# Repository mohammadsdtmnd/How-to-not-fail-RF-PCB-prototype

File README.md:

# How to not fail RF PCB prototype
I've made GPS amplifier for hobby time, it failed. I've learned what I should not have done again to prevent failure. My motivation for doing this was to see the GPS signal spectrum. :) Note I had tried my best to minimize cost. For example by eliminating stensil and soldermask. Though still PCB is metalized with bot layer gnd. I think I could also not making it metalized. Making it stiching with thin wire, instead. Since metalizing caused my manufacturer to prolong a long time.

**You can look at schematic and PCB and see these strength:**

+ Simple
+ High gain
+ Extremely compact design
+ 0.25mm PCB thickness chosen to decrease track and match them to RF amps
+ small footprint which also causes them to be more stable because of less leakage

This compact design chosen to minimize distortion in GPS RF signal.

**PCB Weakness:**
  
+ 0.5mm pitch footprint is small for handsoldering
+ Amplifier package does not have edge lead tail, to make you certain about solder connectivity

But other than foot print and devices package chosen, tools are extremely important:

**Tools weakness:**
  
+ Bulky 60W iron used and caused catastrophy there :(
+ Use of thick solder wire
+ Lower melting point solder plus hot air could help success of assmbling but was missed

**Tools strength:**
  
+ Precise tweezer
+ Good lenz for zooming

And the thing I had really missed was to be patience to waint until accessing at least SMD specialized iron.

**Here is manufactured PCB:**

**Prepaird workbench:**

**First try success:**

**but the secound not:**

I had placed tip of my bulky iron beneath the IC and the resin of PCB burnd!! Though I've been dissapointed. I told OK. I will make the secound PCB with success.
The secound PCB had inherent wrong. It missed one track in sensitive area, Under amplifier. :(

But I managed to handle it with 0.1mm Wire, Low melting solder and Hot air

**And the result was promising:**

Though I've assembled all amplifier with success. Then I tried to place other components with my bulky iron and wire solder. Then another tack removed and caused to one amplifier being detached.

Now next time I will be sure to use smd iron.
Then all components should have more than 1mm pitch for handsoldering. Otherwise I should have sharp tip iron with low melting point solder if possible. Plus patience.

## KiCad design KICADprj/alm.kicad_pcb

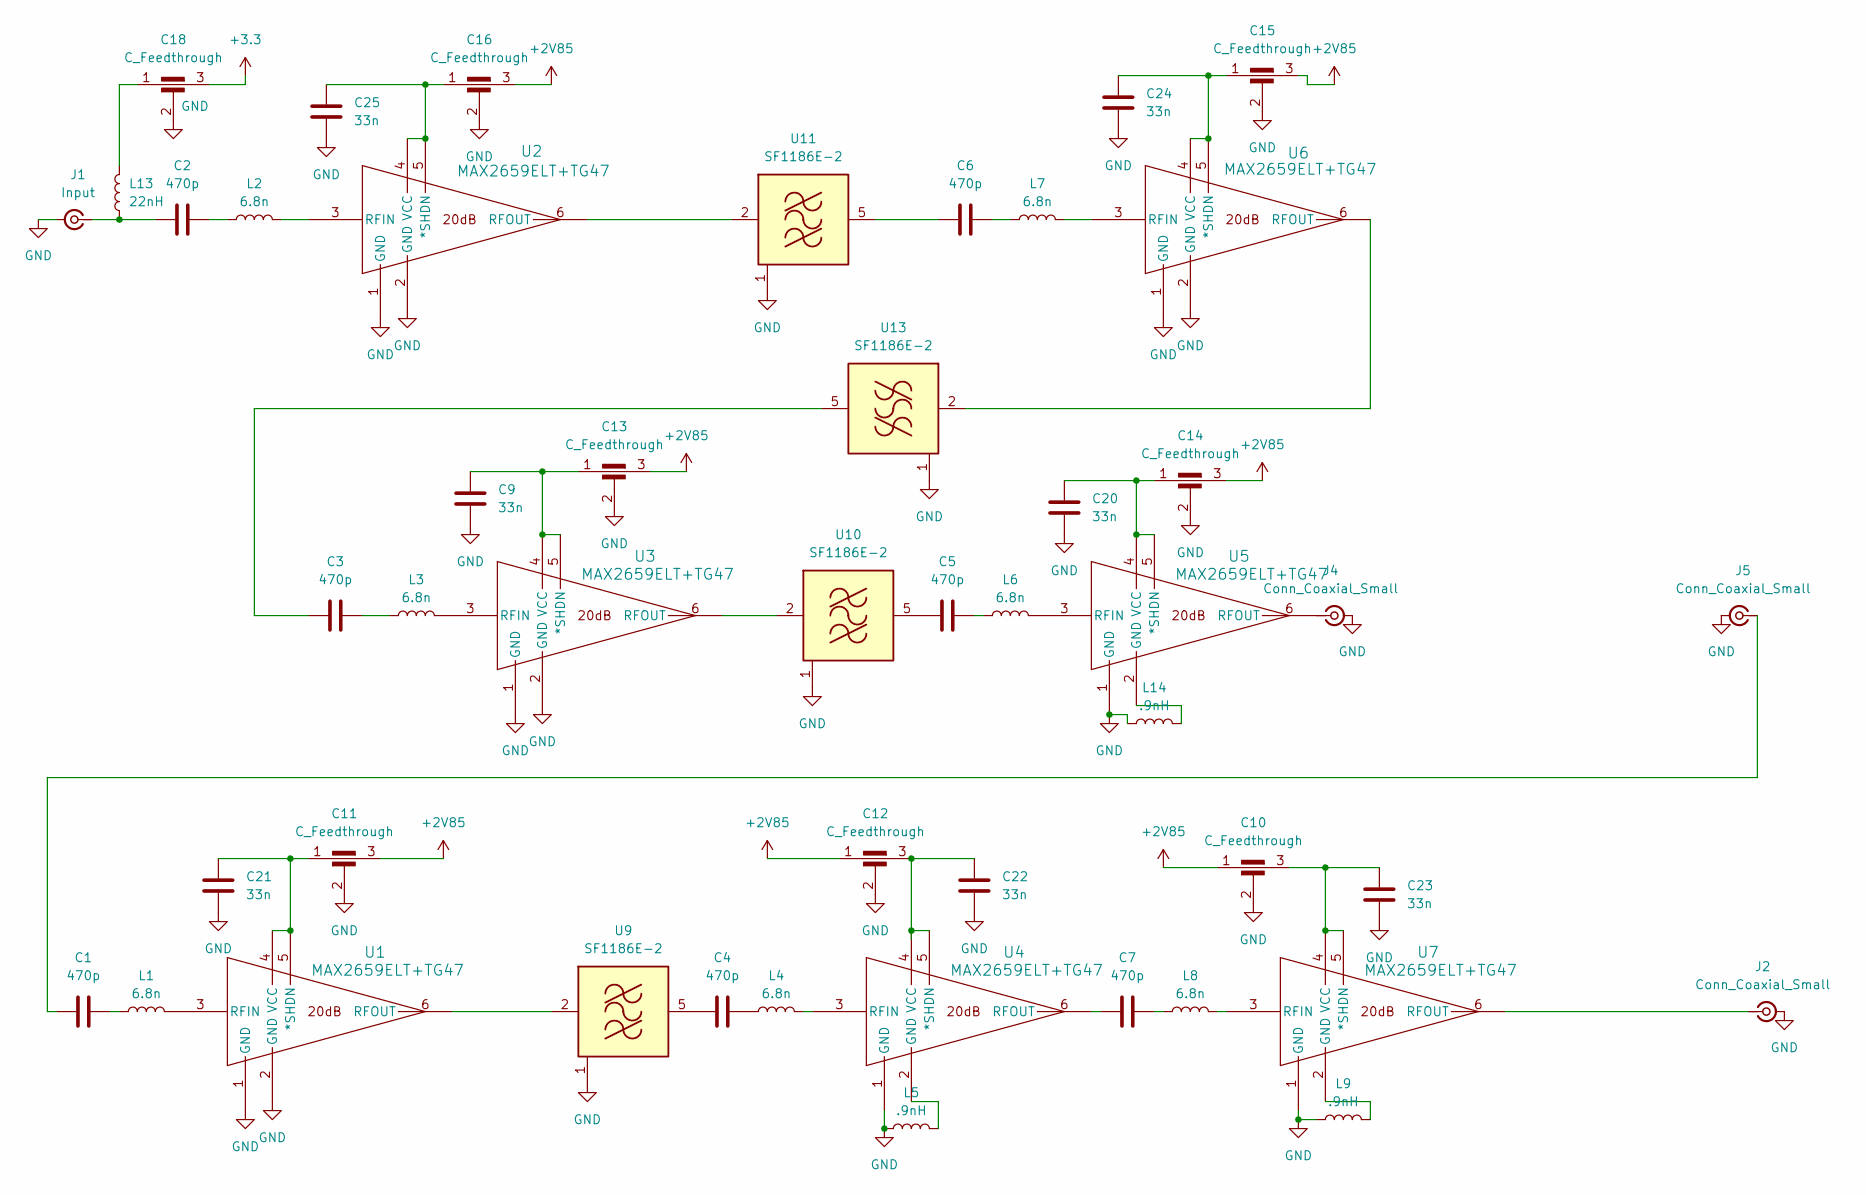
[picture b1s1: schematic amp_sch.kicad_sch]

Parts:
C1, C2, C3, C4, C5, C6, C7: 470p; C_0402_1005Metric_Pad0.74x0.62mm_HandSolder
C9, C20, C21, C22, C23, C24, C25: 33n; C_0402_1005Metric_Pad0.74x0.62mm_HandSolder
C10, C11, C12, C13, C14, C15, C16, C18: C_Feedthrough; FeedThrough_NFM3DPC
J1: Input; SMA_Molex_73251-1153_EdgeMount_Horizontal
J2, J4, J5: Conn_Coaxial_Small; SMA_Molex_73251-1153_EdgeMount_Horizontal
L1, L2, L3, L4, L6, L7, L8: 6.8n; L_0402_1005Metric_Pad0.77x0.64mm_HandSolder
L5, L9, L14: .9nH; L_0402_1005Metric
L13: 22nH; L_0603_1608Metric
U1, U2, U3, U4, U5, U6, U7: MAX2659ELT+TG47; UDFN-6 1.5x1x.75mm
U9, U10, U11, U13: SF1186E-2; Filter_SAW_Epcos_DCC6C_3x3mm

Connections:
+2V85: C10.1, C11.3, C12.1, C13.3, C14.3, C15.3, C16.3; also elsewhere on the board
+3.3: C18.3; also elsewhere on the board
GND: C9.1, C10.2, C11.2, C12.2, C13.2, C14.2, C15.2, C16.2, C18.2, C20.1, C21.1, C22.1, C23.1, C24.1, C25.1, J1.2 (Ext), J2.2 (Ext), J4.2 (Ext), J5.2 (Ext), L5.1, L9.1, L14.1, U1.1 (GND), U1.2 (GND), U2.1 (GND), U2.2 (GND), U3.1 (GND), U3.2 (GND), U4.1 (GND), U5.1 (GND), U6.1 (GND), U6.2 (GND), U7.1 (GND), U9.1 (GND), U9.3 (GND), U9.4 (GND), U9.6 (GND), U10.1 (GND), U10.3 (GND), U10.4 (GND), U10.6 (GND), U11.1 (GND), U11.3 (GND), U11.4 (GND), U11.6 (GND), U13.1 (GND), U13.3 (GND), U13.4 (GND), U13.6 (GND); also elsewhere on the board
unnamed: C1.2, L1.1
unnamed: C2.2, L2.1
unnamed: C3.2, L3.1
unnamed: C4.2, L4.1
unnamed: C5.2, L6.1
unnamed: C6.2, L7.1
unnamed: C7.2, L8.1
unnamed: C18.1, L13.2
unnamed: C2.1, J1.1 (In), L13.1
unnamed: J2.1 (In), U7.6 (RFOUT)
unnamed: J4.1 (In), U5.6 (RFOUT)
unnamed: C1.1, J5.1 (In)
unnamed: L5.2, U4.2 (GND)
unnamed: L9.2, U7.2 (GND)
unnamed: L14.2, U5.2 (GND)
unnamed: C11.1, C21.2, U1.4 (VCC), U1.5 (*SHDN)
unnamed: L1.2, U1.3 (RFIN)
unnamed: U1.6 (RFOUT), U9.2 (IN)
unnamed: C16.1, C25.2, U2.4 (VCC), U2.5 (*SHDN)
unnamed: L2.2, U2.3 (RFIN)
unnamed: C9.2, C13.1, U3.4 (VCC), U3.5 (*SHDN)
unnamed: L3.2, U3.3 (RFIN)
unnamed: C12.3, C22.2, U4.4 (VCC), U4.5 (*SHDN)
unnamed: L4.2, U4.3 (RFIN)
unnamed: C7.1, U4.6 (RFOUT)
unnamed: C14.1, C20.2, U5.4 (VCC), U5.5 (*SHDN)
unnamed: L6.2, U5.3 (RFIN)
unnamed: C15.1, C24.2, U6.4 (VCC), U6.5 (*SHDN)
unnamed: L7.2, U6.3 (RFIN)
unnamed: C10.3, C23.2, U7.4 (VCC), U7.5 (*SHDN)
unnamed: L8.2, U7.3 (RFIN)
unnamed: C4.1, U9.5 (OUT)
unnamed: U3.6 (RFOUT), U10.2 (IN)
unnamed: C5.1, U10.5 (OUT)
unnamed: U2.6 (RFOUT), U11.2 (IN)
unnamed: C6.1, U11.5 (OUT)
unnamed: U6.6 (RFOUT), U13.2 (IN)
unnamed: C3.1, U13.5 (OUT)

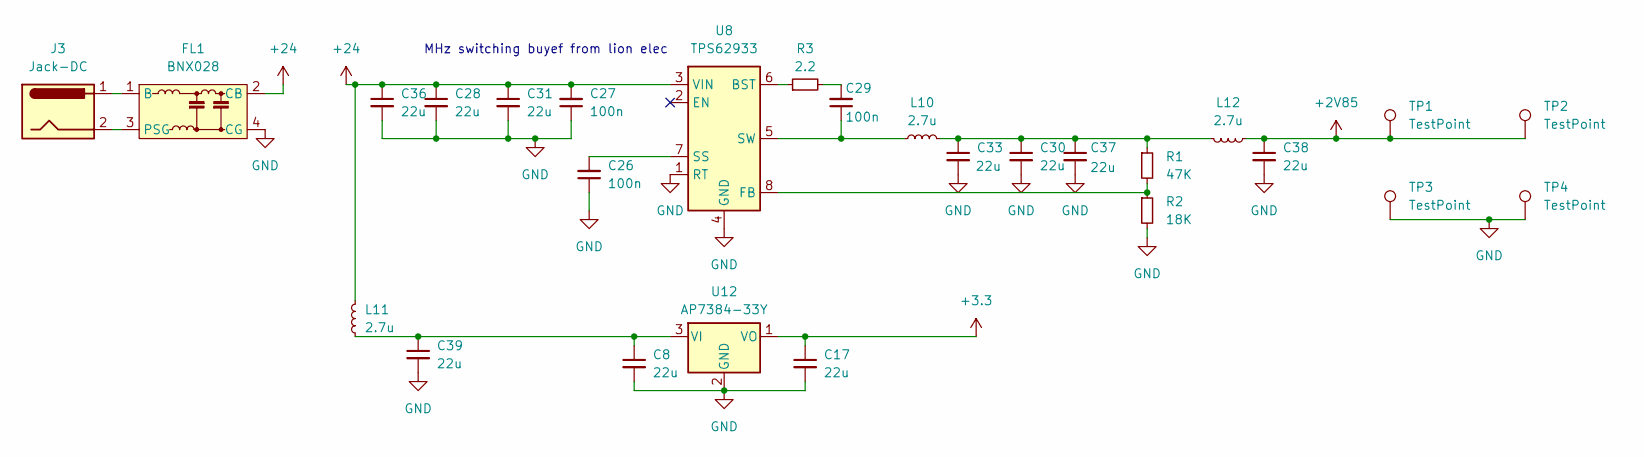
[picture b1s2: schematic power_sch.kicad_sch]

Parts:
C8, C17, C28, C30, C31, C33, C36, C37, C38, C39: 22u; C_0805_2012Metric
C26, C27, C29: 100n; C_0402_1005Metric_Pad0.74x0.62mm_HandSolder
FL1: BNX028; Filter_Murata_BNX025
J3: Jack-DC; BarrelJack_Horizontal
L10, L11, L12: 2.7u; 4x4x2.8mmIND_VLCF4028T-2R7N1R8-2
R1: 47K; R_0402_1005Metric
R2: 18K; R_0402_1005Metric
R3: 2.2; R_0402_1005Metric
TP1, TP2, TP3, TP4: TestPoint; SolderWirePad_1x01_SMD_5x10mm
U8: TPS62933; SOT-583-8
U12: AP7384-33Y; SOT-89-3

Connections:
+2V85: C38.1, L12.1, TP1.1, TP2.1; also elsewhere on the board
+3.3: C17.1, U12.1 (VO); also elsewhere on the board
+24: C27.2, C28.1, C31.1, C36.1, FL1.2 (CB), L11.2, U8.3 (VIN)
GND: C8.2, C17.2, C26.1, C27.1, C28.2, C30.2, C31.2, C33.2, C36.2, C37.2, C38.2, C39.2, FL1.4 (CG), R2.2, TP3.1, TP4.1, U8.1 (RT), U8.4 (GND), U12.2 (GND); also elsewhere on the board
unnamed: C29.2, R3.2
unnamed: C30.1, C33.1, C37.1, L10.2, L12.2, R1.1
unnamed: FL1.1 (B), J3.1
unnamed: FL1.3 (PSG), J3.2
unnamed: R3.1, U8.6 (BST)
unnamed: R1.2, R2.1, U8.8 (FB)
unnamed: C26.2, U8.7 (SS)
unnamed: C29.1, L10.1, U8.5 (SW)
unnamed: C8.1, C39.1, L11.1, U12.3 (VI)

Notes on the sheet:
MHz switching buyef from lion elec

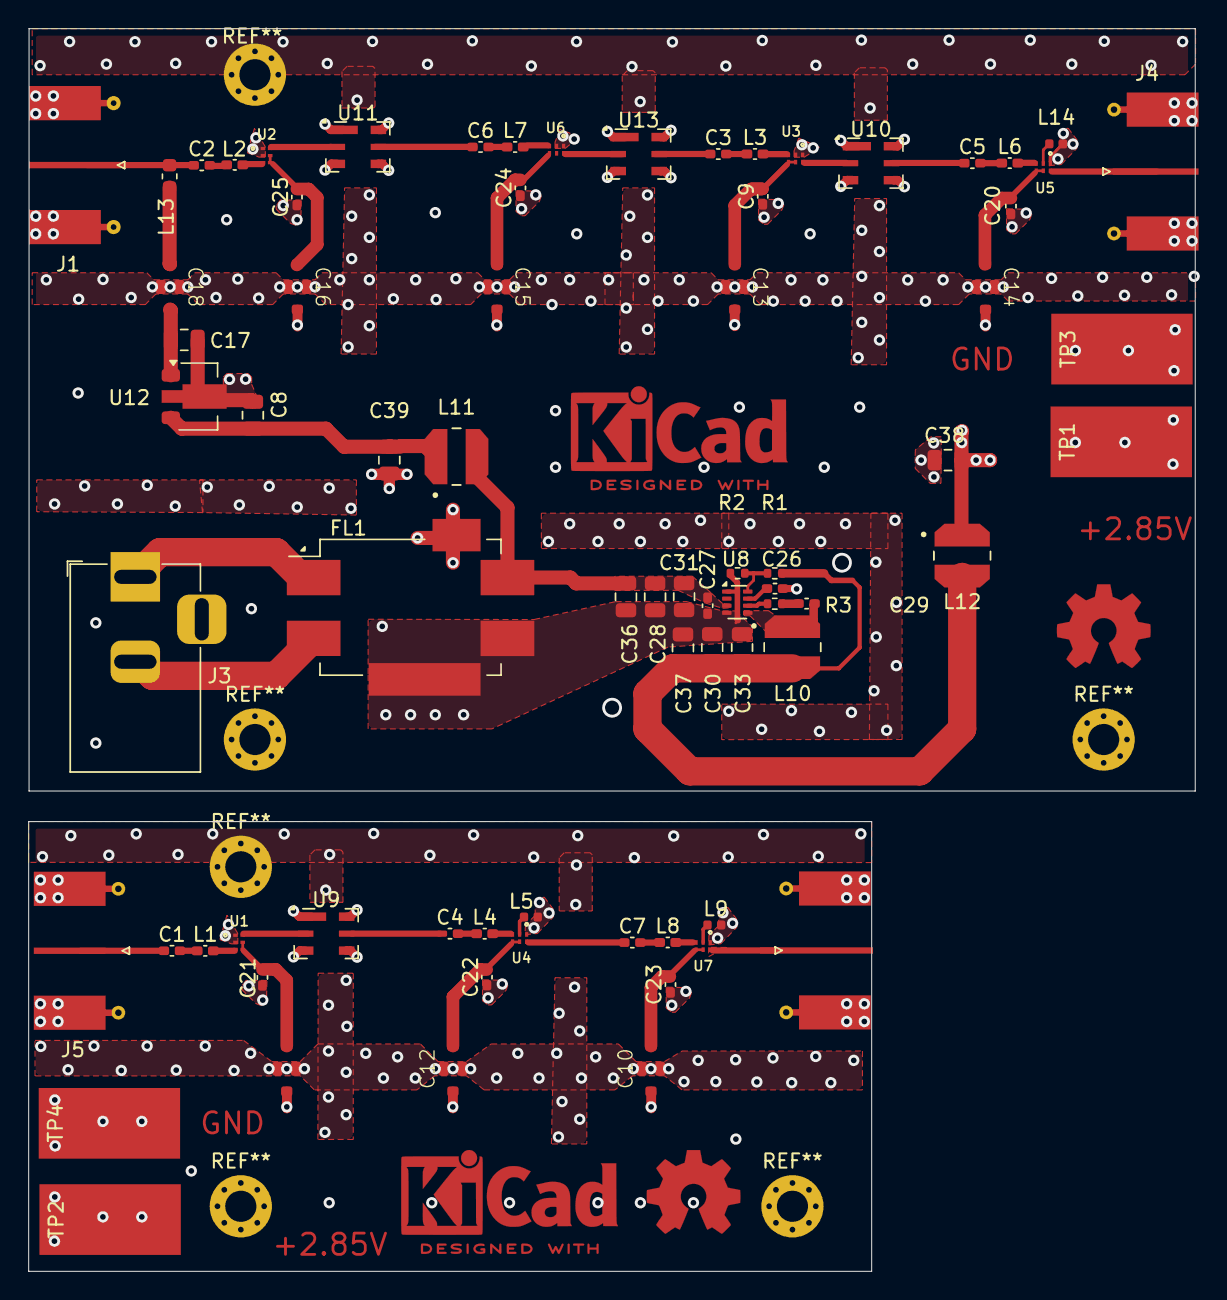
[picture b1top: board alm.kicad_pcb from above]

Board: 4 copper layers, 82.5 x 87.9 mm, 75 parts (0 on the bottom side), 51 nets.

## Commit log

2025-09-08 Create Images
    Images of projects are here
2025-09-08 Update README.md
    Added experience
2025-09-08 Update README.md
    compressed half of images
2025-09-08 Update README.md
    compressing more pictures
2025-09-08 Update README.md
    image compression finished
2025-09-08 Update README.md
    Adjusting layout
2025-09-08 Update README.md
    More data about PCB layer and its fab options added in top paragraph.
2025-09-08 Create KiCadProj
    Kicad project files here
2025-09-08 Delete KiCadProj
    Deleted redundant files
2025-09-08 create project folder
2025-09-08 Create 1
2025-09-08 added project
